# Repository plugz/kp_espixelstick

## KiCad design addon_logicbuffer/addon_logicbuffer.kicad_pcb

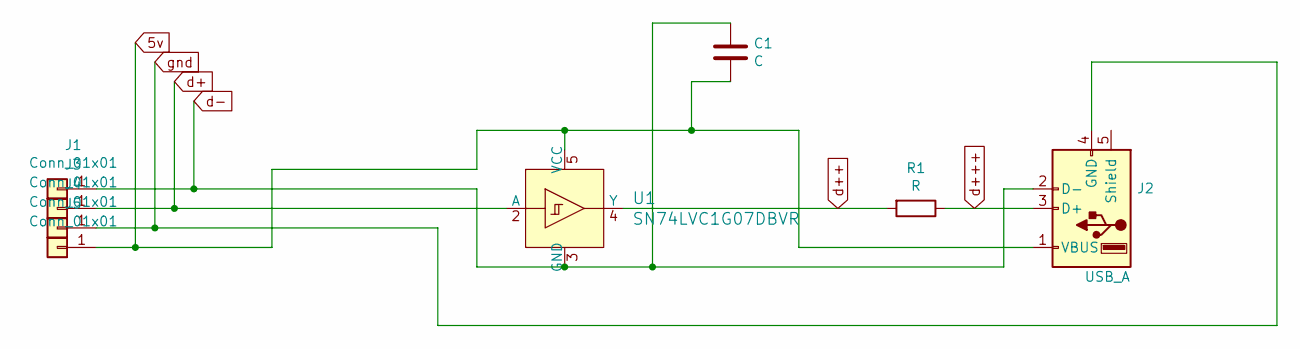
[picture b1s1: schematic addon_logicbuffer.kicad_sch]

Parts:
C1: C; C_0402_1005Metric
J1, J3, J4, J5: Conn_01x01; PinHeader_1x01_P2.00mm_Vertical
J2: USB_A; USB_A_Molex_67643_Horizontal
R1: R; R_0603_1608Metric_Pad1.05x0.95mm_HandSolder
U1: SN74LVC1G07DBVR; SOT-753; MPN SN74LVC1G07DBVR; Digi-Key_PN 296-8485-1-ND

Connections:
5v: C1.2, J2.1 (VBUS), J5.1, U1.5 (VCC)
d+: J3.1, U1.2 (A)
d++: R1.2, U1.4 (Y)
d+++: J2.3 (D+), R1.1
d-: C1.1, J1.1, J2.2 (D-), U1.3 (GND)
gnd: J2.4 (GND), J4.1

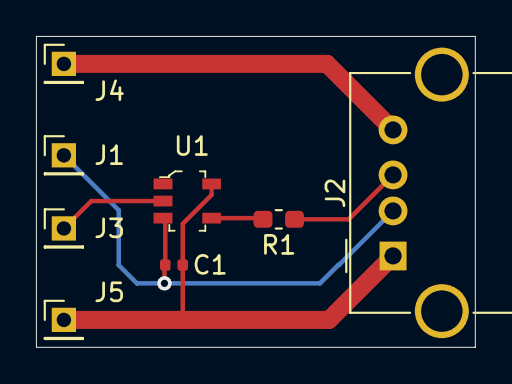
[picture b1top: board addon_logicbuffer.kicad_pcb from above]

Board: 2 copper layers, 24.4 x 17.3 mm, 8 parts (0 on the bottom side), 6 nets.

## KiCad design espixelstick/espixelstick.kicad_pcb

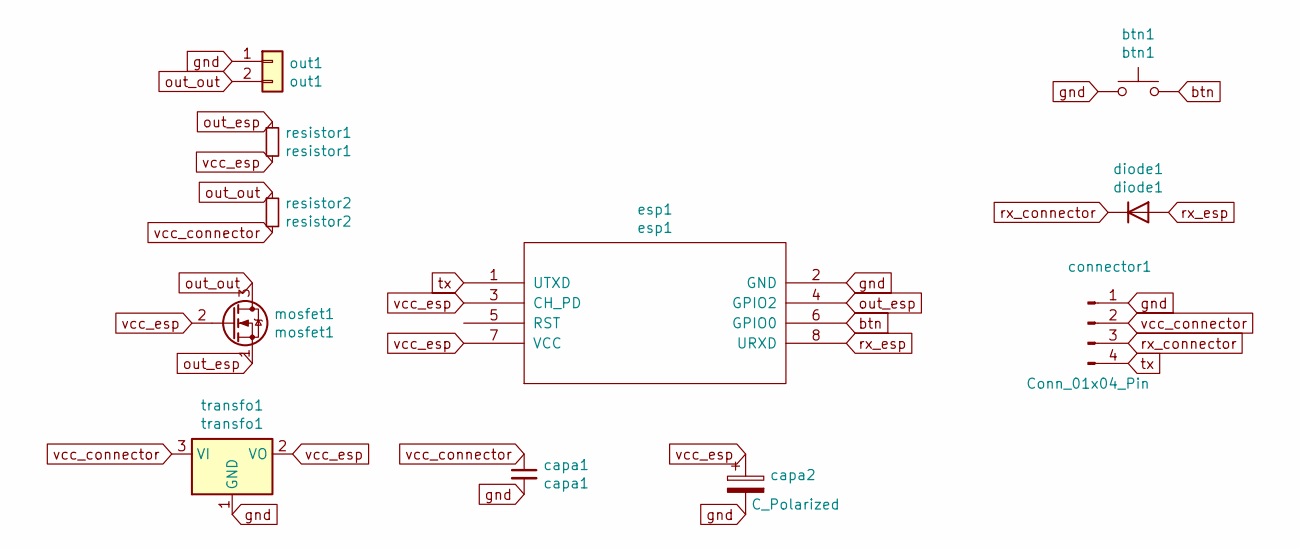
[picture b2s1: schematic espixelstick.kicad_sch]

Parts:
btn1: btn1; SW_PUSH_6mm
capa1: capa1; C_Disc_D3.0mm_W1.6mm_P2.50mm
capa2: C_Polarized; CP_Radial_D5.0mm_P2.00mm
connector1: Conn_01x04_Pin; Pin_Header_Straight_1x04_Pitch2.54mm
diode1: diode1; D_DO-35_SOD27_P7.62mm_Horizontal
esp1: esp1; ESP-01
mosfet1: mosfet1; TO-92_Inline_Wide
out1: out1; Pin_Header_Straight_1x02_Pitch2.54mm
resistor1: resistor1; R_Axial_DIN0207_L6.3mm_D2.5mm_P7.62mm_Horizontal
resistor2: resistor2; R_Axial_DIN0207_L6.3mm_D2.5mm_P7.62mm_Horizontal
transfo1: transfo1; TO-220-3_Vertical

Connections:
btn: btn1.2, esp1.6 (GPIO0)
gnd: btn1.1, capa1.2, capa2.2, connector1.1, esp1.2 (GND), out1.1, transfo1.1 (GND)
out_esp: esp1.4 (GPIO2), mosfet1.1 (S), resistor1.1
out_out: mosfet1.3 (D), out1.2, resistor2.1
rx_connector: connector1.3, diode1.1 (K)
rx_esp: diode1.2 (A), esp1.8 (URXD)
tx: connector1.4, esp1.1 (UTXD)
vcc_connector: capa1.1, connector1.2, resistor2.2, transfo1.3 (VI)
vcc_esp: capa2.1, esp1.3 (CH_PD), esp1.7 (VCC), mosfet1.2 (G), resistor1.2, transfo1.2 (VO)

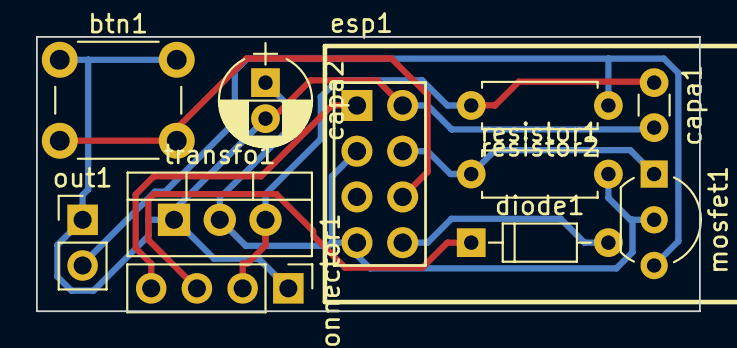
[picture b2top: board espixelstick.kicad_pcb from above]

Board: 2 copper layers, 36.8 x 15.2 mm, 11 parts (0 on the bottom side), 9 nets.

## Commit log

2020-03-06 init commit
2020-03-06 add files
2020-07-15 add addon_logicbuffer
2023-08-05 move espixelstick to its own folder
2023-08-05 update to kicad7
2023-08-05 add 7.0 files, fix missing symbols
